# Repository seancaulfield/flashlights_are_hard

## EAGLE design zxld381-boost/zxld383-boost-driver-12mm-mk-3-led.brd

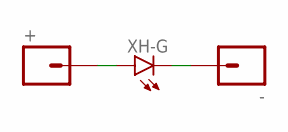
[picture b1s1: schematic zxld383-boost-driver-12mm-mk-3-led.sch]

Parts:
+: M01PTH-1.2MM; 1X01-1.2MM
-: M01PTH-1.2MM-NS; 1X01-1.2MM-NS
XH-G: LEDXH-G; CREE-XLAMP-XH-G

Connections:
GND: -.P$1, XH-G.K (C), XH-G.K@1 (C), XH-G.K@2 (C), XH-G.K@3 (C), XH-G.K@4 (C), XH-G.K@5 (C), XH-G.K@6 (C), XH-G.K@7 (C), XH-G.K@8 (C)
VCC: +.P$1, XH-G.A

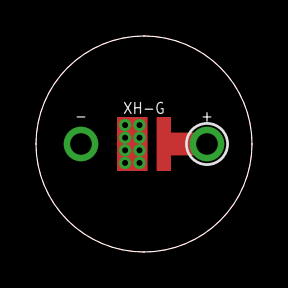
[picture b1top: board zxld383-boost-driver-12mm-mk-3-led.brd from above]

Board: 2 copper layers, 12.0 x 12.0 mm, 3 parts (0 on the bottom side), 2 nets.

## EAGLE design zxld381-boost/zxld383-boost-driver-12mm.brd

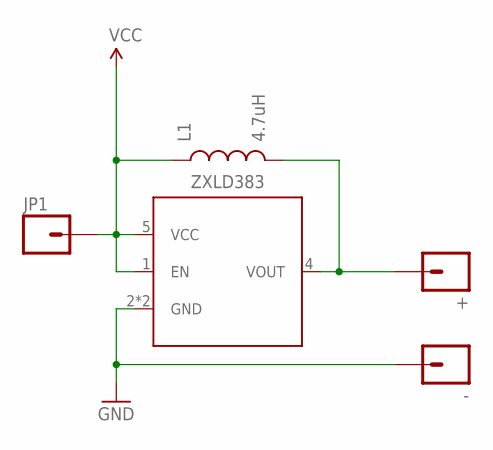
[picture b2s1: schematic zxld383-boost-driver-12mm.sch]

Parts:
+: M01PTH-1.2MM; 1X01-1.2MM
-: M01PTH-1.2MM-NS; 1X01-1.2MM-NS
JP1: M01NOT-A-VIA-NOPE; 1X01_NOSILK_NOSTOP
L1: 4.7uH; 1007
ZXLD383: ZXLD383; TSOT-23-5

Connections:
GND: -.P$1, ZXLD383.2 (GND), ZXLD383.3 (GND)
VCC: JP1.P$1, L1.1, ZXLD383.1 (EN), ZXLD383.5 (VCC)
VOUT: +.P$1, L1.2, ZXLD383.4 (VOUT)

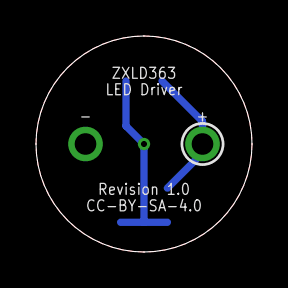
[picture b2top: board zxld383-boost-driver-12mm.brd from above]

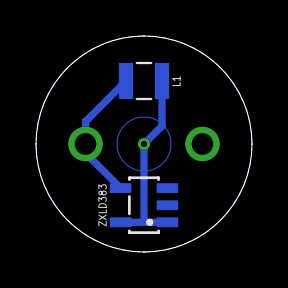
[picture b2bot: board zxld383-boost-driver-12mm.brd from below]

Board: 2 copper layers, 12.0 x 12.0 mm, 5 parts (2 on the bottom side), 3 nets.

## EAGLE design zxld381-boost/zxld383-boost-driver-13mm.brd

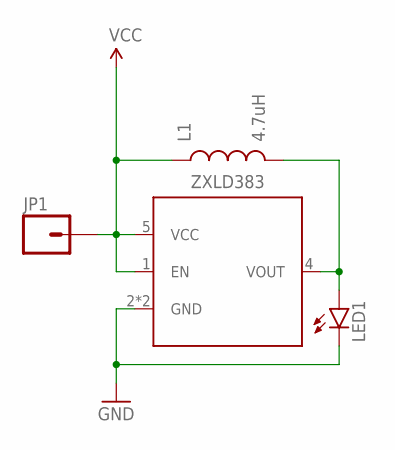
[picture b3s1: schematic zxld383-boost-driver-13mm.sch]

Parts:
JP1: M01NOT-A-VIA-NOPE; 1X01_NOSILK_NOSTOP
L1: 4.7uH; 1007
LED1: LED10MM
ZXLD383: ZXLD383; TSOT-23-5

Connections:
GND: LED1.C, ZXLD383.2 (GND), ZXLD383.3 (GND)
VCC: JP1.P$1, L1.1, ZXLD383.1 (EN), ZXLD383.5 (VCC)
VOUT: L1.2, LED1.A, ZXLD383.4 (VOUT)

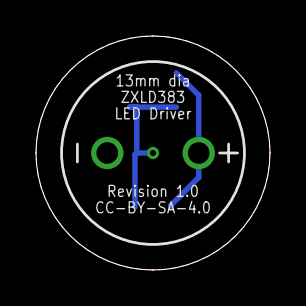
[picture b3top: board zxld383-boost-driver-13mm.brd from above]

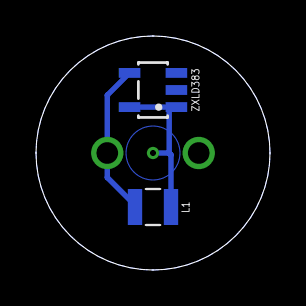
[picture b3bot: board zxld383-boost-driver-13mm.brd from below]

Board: 2 copper layers, 13.0 x 13.0 mm, 4 parts (2 on the bottom side), 3 nets.

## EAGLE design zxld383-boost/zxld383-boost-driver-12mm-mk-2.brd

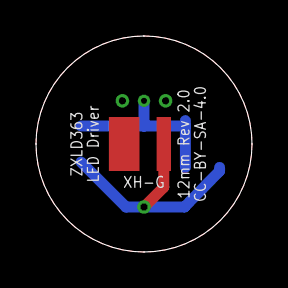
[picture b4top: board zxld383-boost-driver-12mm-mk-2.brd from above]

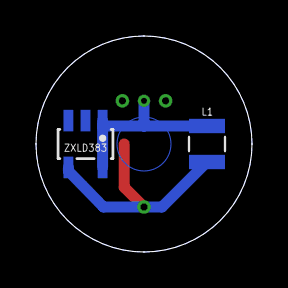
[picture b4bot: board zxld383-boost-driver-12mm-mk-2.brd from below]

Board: 2 copper layers, 12.0 x 12.0 mm, 4 parts (2 on the bottom side), 3 nets.

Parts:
JP1: M01NOT-A-VIA-NOPE; 1X01_NOSILK_NOSTOP
L1: 4.7uH; 1007
XH-G: LEDXH-G; CREE-XLAMP-XH-G
ZXLD383: ZXLD383; TSOT-23-5

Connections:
GND: XH-G.K, ZXLD383.2, ZXLD383.3
VCC: JP1.P$1, L1.1, ZXLD383.1, ZXLD383.5
VOUT: L1.2, XH-G.A, ZXLD383.4

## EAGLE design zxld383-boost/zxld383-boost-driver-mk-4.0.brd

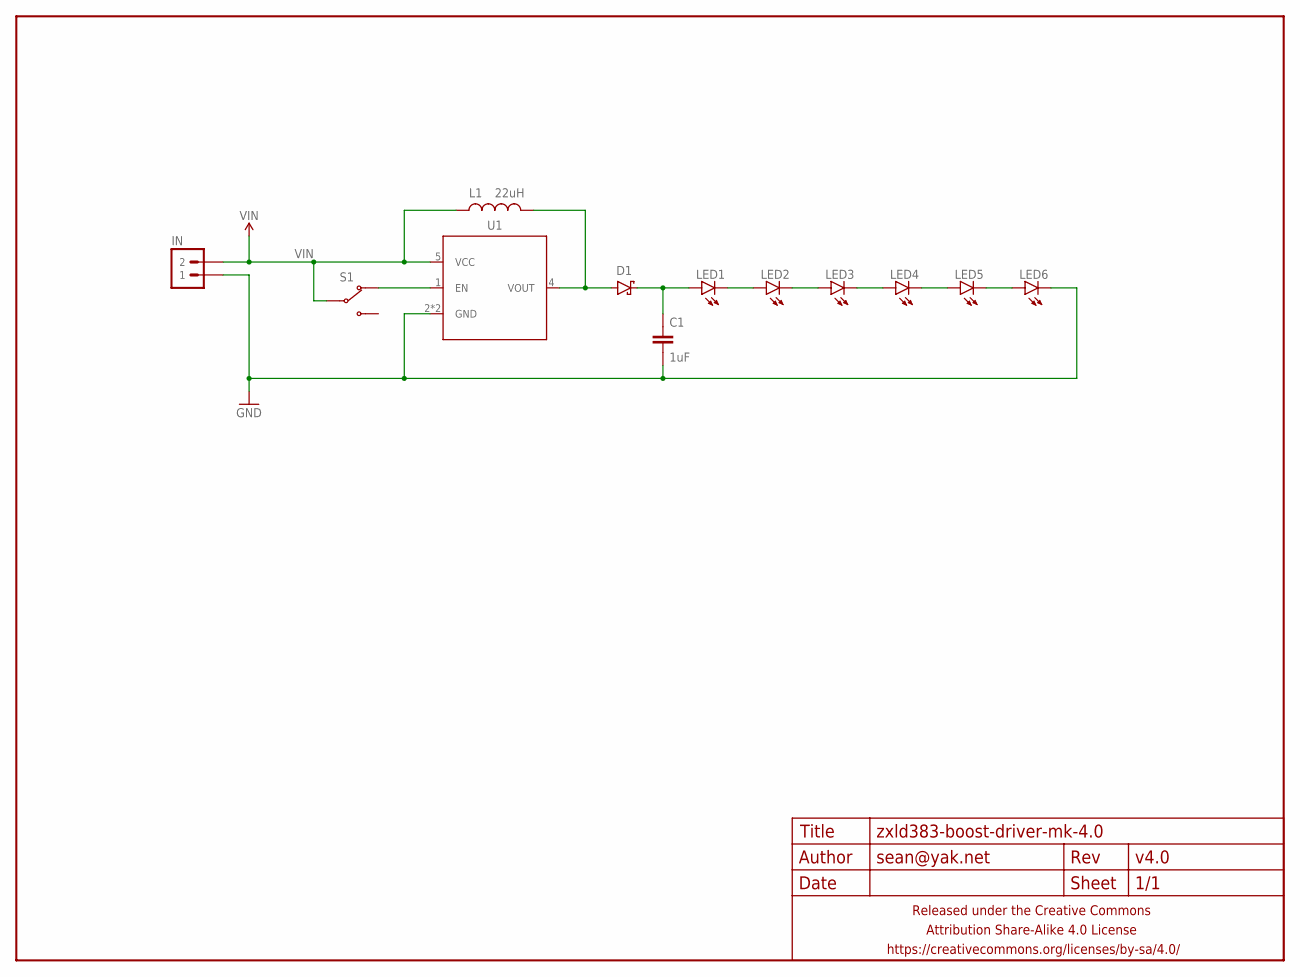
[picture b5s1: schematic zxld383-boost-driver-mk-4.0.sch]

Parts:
C1: 1uF; C0603-TIGHTER
D1: DIODE-SCHOTTKYSOD323; SOD323-SCHOTTKY
FRAME1: FRAME-LETTERNO_PACKAGE; DUMMY
IN: M02PTH-CENTERED-R+; 1X02-CENTER-R+
L1: 22uH; L0603
LED1, LED2, LED3, LED4, LED5, LED6: LED5MM_SHORTPADS
S1: SWITCH-SPDTSMD-RA; SWITCH-SPDT-SMD-RA
U1: ZXLD383; TSOT-23-5

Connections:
GND: C1.2, IN.1, LED6.K (C), U1.2 (GND), U1.3 (GND)
unnamed: S1.3 (NC), U1.1 (EN)
unnamed: LED1.K (C), LED2.A
unnamed: D1.A, L1.2, U1.4 (VOUT)
unnamed: C1.1, D1.C, LED1.A
unnamed: LED2.K (C), LED3.A
unnamed: LED3.K (C), LED4.A
unnamed: LED4.K (C), LED5.A
unnamed: LED5.K (C), LED6.A
VIN: IN.2, L1.1, S1.2 (COM), U1.5 (VCC)

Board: 2 copper layers, 13 parts (0 on the bottom side), 10 nets, no tracks yet.

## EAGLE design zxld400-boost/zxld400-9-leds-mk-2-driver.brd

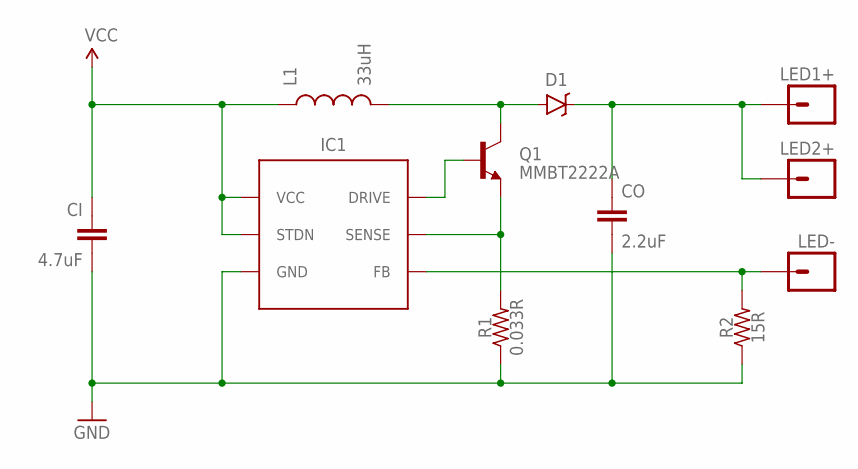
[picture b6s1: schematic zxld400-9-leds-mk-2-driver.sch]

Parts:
CI: 4.7uF; C0805
CO: 2.2uF; C0805
D1: DIODE-SCHOTTKYSMA; SMA-DIODE-SCHOTTKY
IC1: ZXSC400; SOT23-6
L1: 33uH; TAIYO-YUDEN-30XX
LED1+, LED2+: M01PTH; 1X01
LED-: M01PTH; 1X01
Q1: MMBT2222A; SOT23-3
R1: 0.033R; R0805
R2: 15R; R0603

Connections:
GND: CI.2, CO.2, IC1.2 (GND), R1.1, R2.1
LED+: CO.1, D1.C, LED1+.1, LED2+.1
LED-: IC1.5 (FB), LED-.1, R2.2
unnamed: D1.A, L1.2, Q1.3 (C)
unnamed: IC1.6 (DRIVE), Q1.1 (B)
unnamed: IC1.4 (SENSE), Q1.2 (E), R1.2
VCC: CI.1, IC1.1 (VCC), IC1.3 (STDN), L1.1

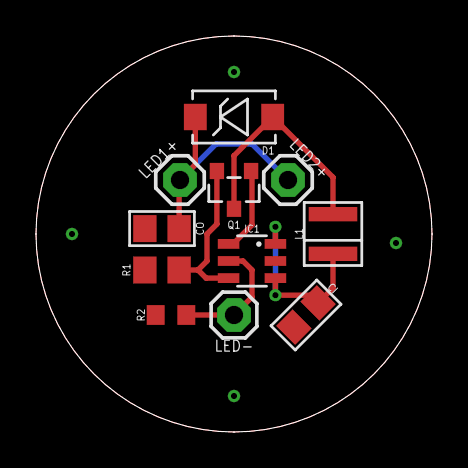
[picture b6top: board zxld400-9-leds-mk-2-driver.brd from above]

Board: 2 copper layers, 22.0 x 22.0 mm, 11 parts (0 on the bottom side), 7 nets.

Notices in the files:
zxld381-boost/zxld383-boost-driver-12mm.brd:
CC-BY-SA-4.0
parts and their libraries:
a_parts: Released under the Creative Commons Attribution Share-Alike 4.0 License
a_parts: https://creativecommons.org/licenses/by-sa/4.0
a_parts: Released under the Creative Commons
